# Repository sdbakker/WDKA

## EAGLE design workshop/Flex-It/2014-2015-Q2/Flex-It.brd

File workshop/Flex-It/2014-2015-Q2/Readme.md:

# Flex-It

## What are we going to make?
 * A tiger touch 'tattoo'
 * Design files: https://github.com/sdbakker/WDKA/tree/master/workshop/Flex-It/2014-2015-Q2
   * Flex-It.sch: this is the schematic of the electronic circuit
   * Flex-It.brd: board layout (this will be your circuit design)
   * Flex-It-routed.brd: this is an example board layout already routed

## First create a circuit and layout
 * [CadSoft eagle](http://www.cadsoftusa.com/)
 * [KiCad](http://www.kicad-pcb.org/display/KICAD/KiCad+EDA+Software+Suite)
 * [Fritzing](http://fritzing.org/home/)

## Getting your circuit on a flexible circuit board at home
 * [Using a cutting plotter](http://www.kobakant.at/DIY/?p=5371)
 * [Using toner transfer method](http://www.instructables.com/id/Cheap-and-Easy-Toner-Transfer-for-PCB-Making/) (don't forget to mirror the image)
 * [Sharpie](http://www.sharpie.com/Pages/GlobalLanding.aspx)
 * [Using a solid ink printer](http://www.instructables.com/id/DIY-Flexible-Printed-Circuits/step2/Use-a-solid-ink-printer/) (don't need to mirror)

## Etching
 * We will use Iron(III)Chloride or Fe3CL, this removes all the copper not covered.
 * Be very careful, these are nasty chemicals!!

## Adding the components
 * Solder the components on your circuit board
 * We are using [SMD components](https://en.wikipedia.org/wiki/Surface-mount_technology)!
 * Be precise, it is easy to make a short circuit as we do not have a solder mask

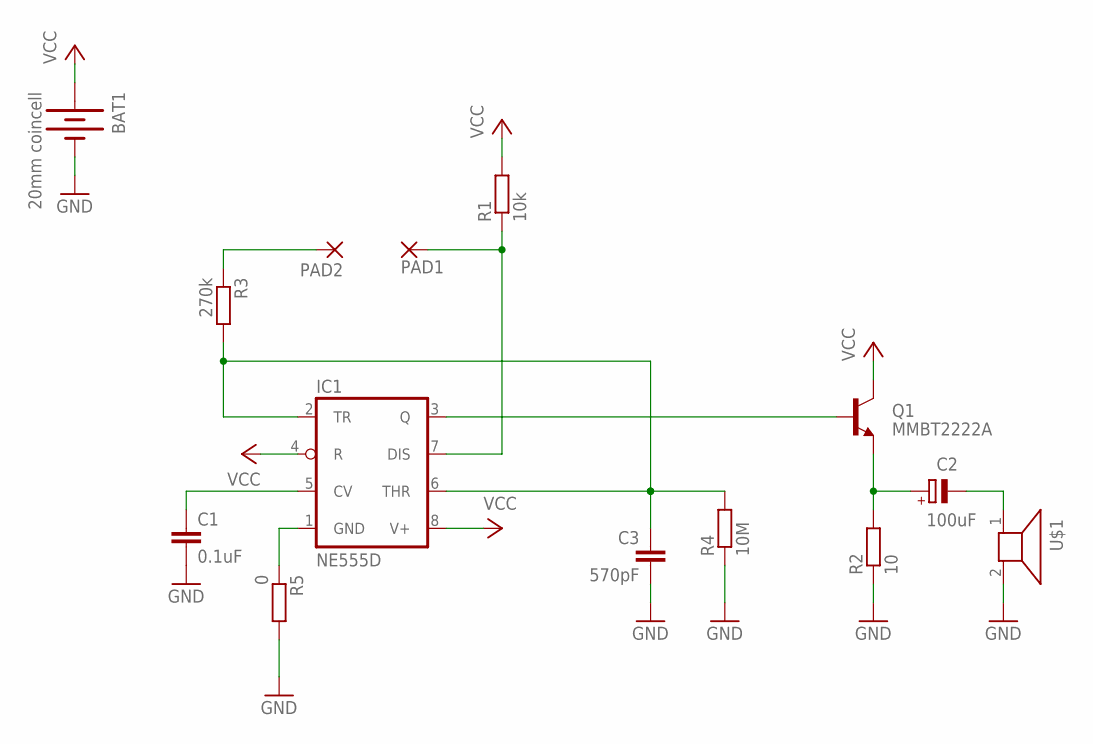
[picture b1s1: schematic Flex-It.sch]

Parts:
BAT1: 20mm coincell; BATTCON_20MM_4LEGS; DIGIKEY BK-912-CT-ND
C1: 0.1uF; C1206K
C2: 100uF; SMC_B
C3: 570pF; C1206K
IC1: NE555D; SO08
PAD1, PAD2: WIREPADSMD1,27-254; SMD1,27-2,54
Q1: MMBT2222A; SOT23-3
R1: 10k; R1206
R2: 10; R1206
R3: 270k; R1206
R4: 10M; R1206
R5: 0; R1206
U$1: PS603SPK; PS603

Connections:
GND: BAT1.2 (-), C1.2, C3.2, IC1.1 (GND), R2.1, R4.1, R5.1, R5.2, U$1.2
unnamed: C1.1, IC1.5 (CV)
unnamed: C3.1, IC1.2 (TR), IC1.6 (THR), R3.2, R4.2
unnamed: IC1.3 (Q), Q1.1 (B)
unnamed: C2.-, U$1.1
unnamed: C2.+, Q1.2 (E), R2.2
TOUCH1: IC1.7 (DIS), PAD1.1, R1.1
TOUCH2: PAD2.1, R3.1
VCC: BAT1.1 (+), BAT1.3 (+), BAT1.P$1 (+), BAT1.P$2 (+), IC1.4 (R), IC1.8 (V+), Q1.3 (C), R1.2

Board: 2 copper layers, 14 parts (0 on the bottom side), 9 nets, no tracks yet.

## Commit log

2014-11-25 plotclock arduino workshop reader
2014-11-25 moved to workshops
2014-11-25 added some more links, servo, led
2014-11-25 arduino image
2014-11-25 changed plotclock_arduino.md to readme.md
2014-12-02 Added week 2
2014-12-09 Added analog
2014-12-16 Added Screenscraping
2014-12-16 firsttrack
2014-12-18 Added 3D printing
2015-01-06 Added gitignore
2015-01-06 Added Flex-it template
2015-01-06 Thicker traces
2015-01-06 No thermals, larger isolation in polygons
2015-01-06 Added readme
2015-01-06 Added circuit image
2015-01-20 added arduino basis 1

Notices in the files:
parts and their libraries:
SparkFun-DiscreteSemi: Licensing: Creative Commons ShareAlike 4.0 International - https://creativecommons.org/licenses/by-sa/4.0
